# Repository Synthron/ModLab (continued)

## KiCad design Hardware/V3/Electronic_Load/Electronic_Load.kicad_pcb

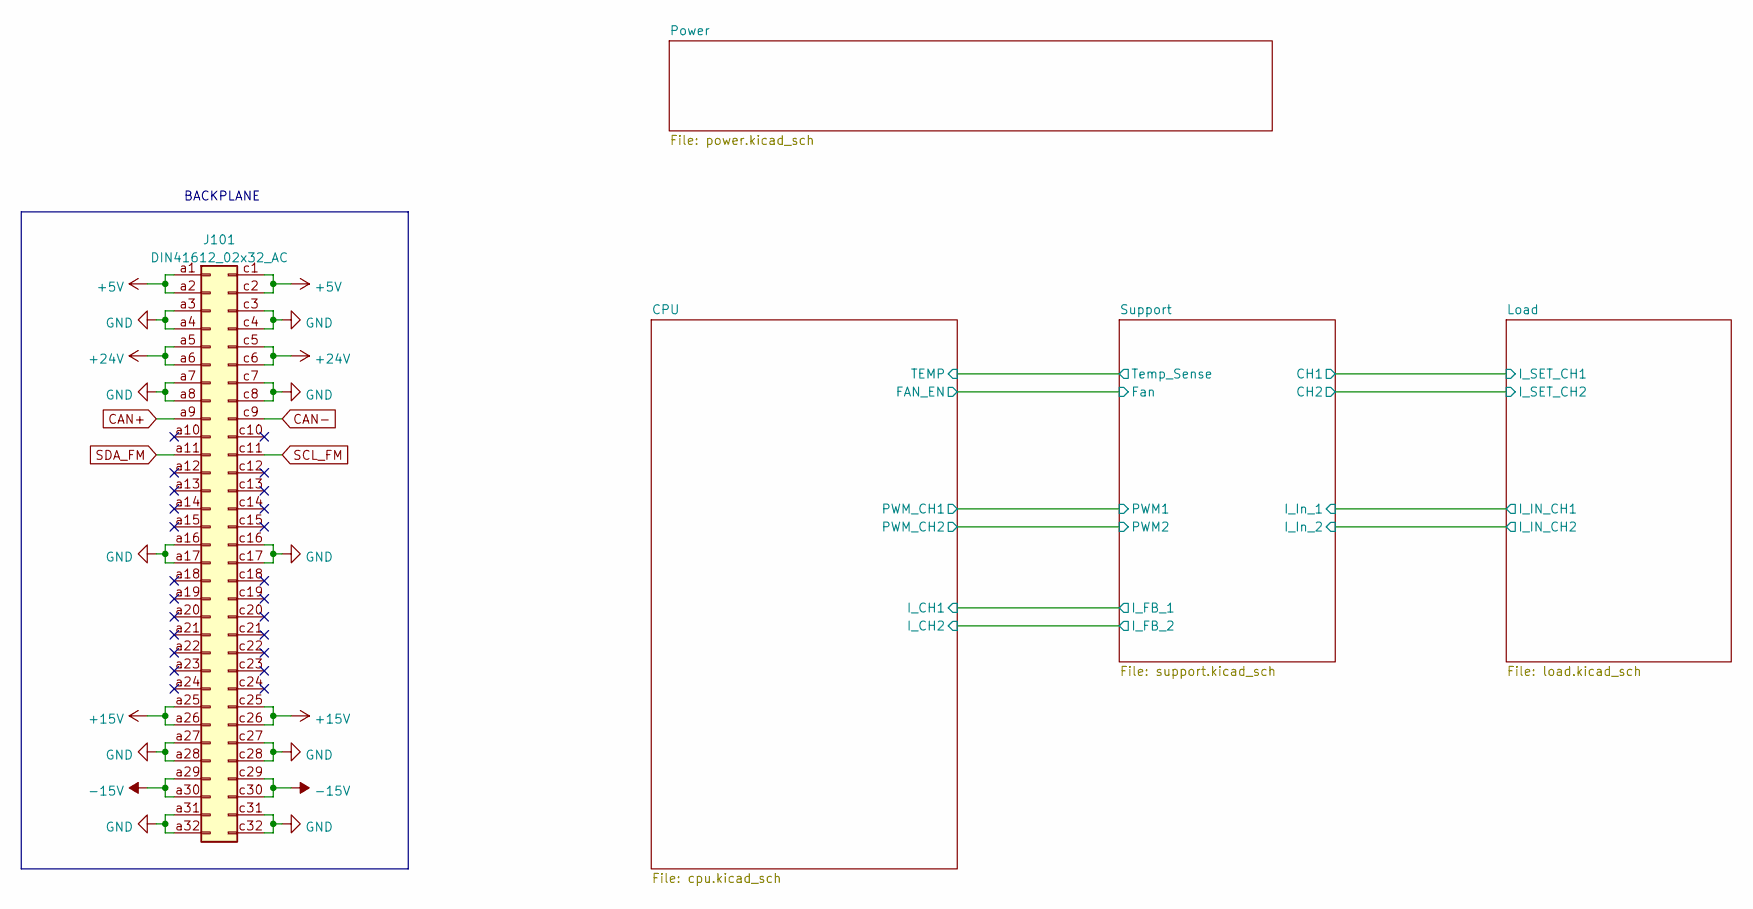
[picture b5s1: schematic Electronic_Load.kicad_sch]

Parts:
J101: DIN41612_02x32_AC; VG64_Euro

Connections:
+5V: J101.a1, J101.a2, J101.c1, J101.c2; also elsewhere on the board
+15V: J101.a25, J101.a26, J101.c25, J101.c26; also elsewhere on the board
+24V: J101.a5, J101.a6, J101.c5, J101.c6; also elsewhere on the board
-15V: J101.a29, J101.a30, J101.c29, J101.c30; also elsewhere on the board
CAN+: J101.a9; also elsewhere on the board
CAN-: J101.c9; also elsewhere on the board
GND: J101.a3, J101.a4, J101.a7, J101.a8, J101.a16, J101.a17, J101.a27, J101.a28, J101.a31, J101.a32, J101.c3, J101.c4, J101.c7, J101.c8, J101.c16, J101.c17, J101.c27, J101.c28, J101.c31, J101.c32; also elsewhere on the board
SCL_FM: J101.c11; also elsewhere on the board
SDA_FM: J101.a11; also elsewhere on the board

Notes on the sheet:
BACKPLANE

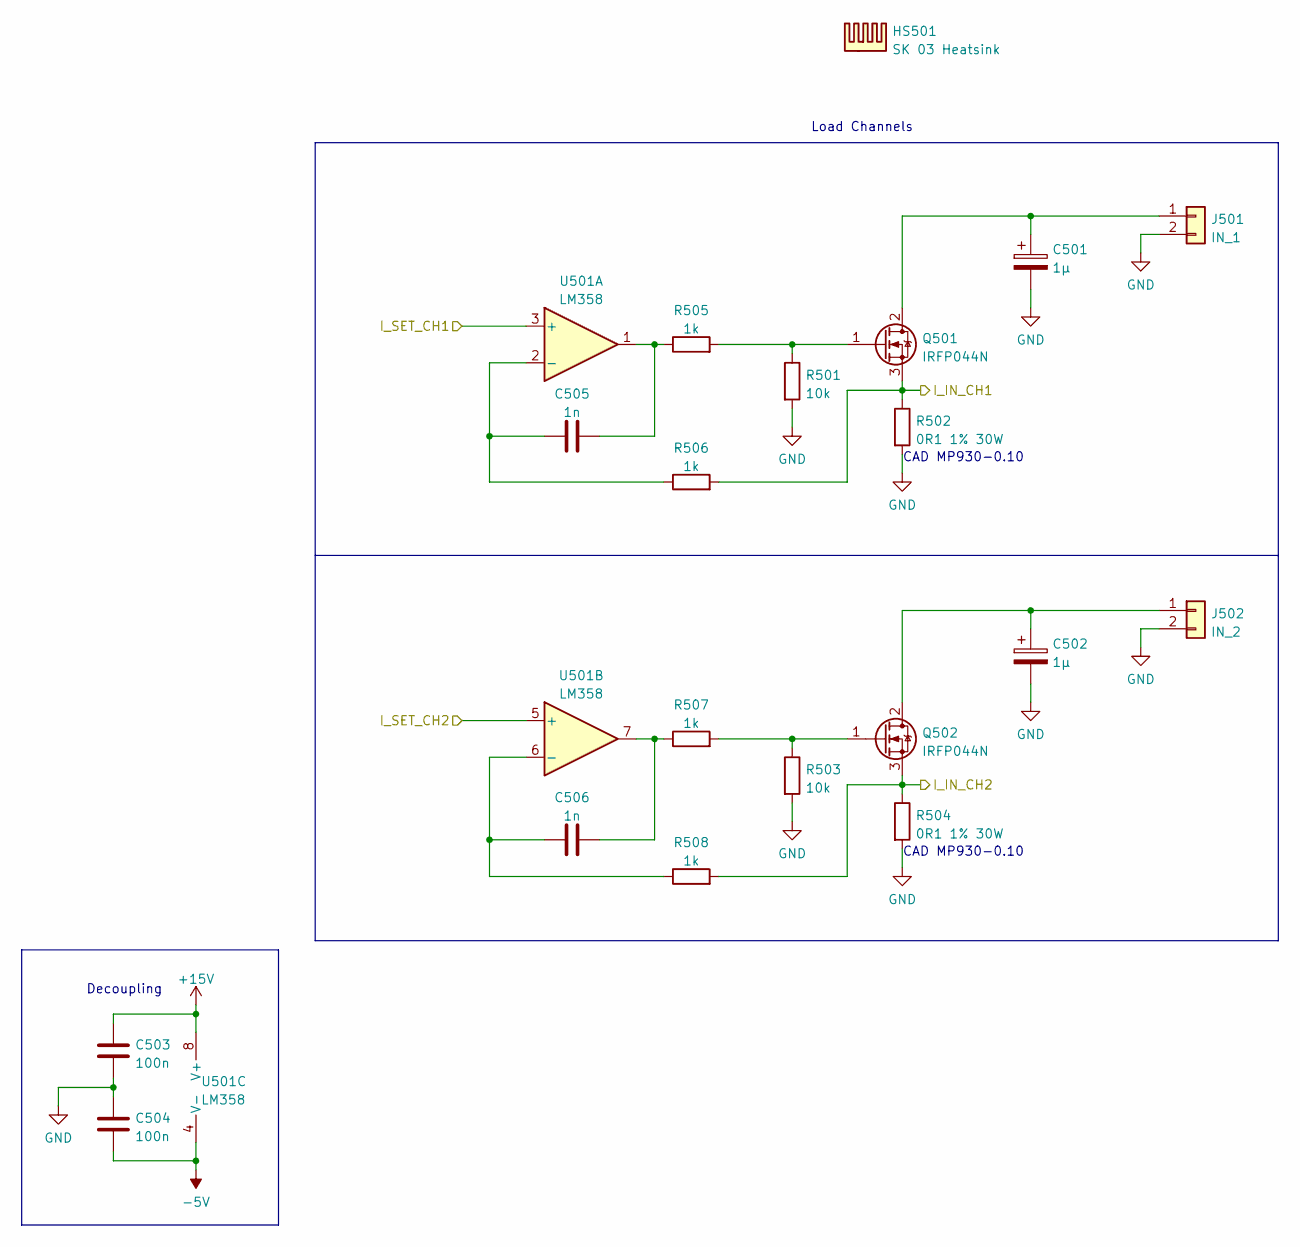
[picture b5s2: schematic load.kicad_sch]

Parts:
C501, C502: 1µ; CP_Radial_D5.0mm_P2.50mm
C503, C504: 100n; C_0805_2012Metric
C505, C506: 1n; C_0805_2012Metric
HS501: SK 03 Heatsink; SK-03
J501: IN_1; PinHeader_1x02_P2.54mm_Vertical
J502: IN_2; PinHeader_1x02_P2.54mm_Vertical
Q501, Q502: IRFP044N; TO-247-3_Horizontal_TabUp
R501, R503: 10k; R_0805_2012Metric
R502, R504: 0R1 1% 30W; TO-220F-2_Horizontal_TabUp
R505, R506, R507, R508: 1k; R_0805_2012Metric
U501: LM358; SOIC-8_3.9x4.9mm_P1.27mm

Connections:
+15V: C503.1, U501.8 (V+); also elsewhere on the board
-5V: C504.2, U501.4 (V-); also elsewhere on the board
/Load/I_IN_CH1: Q501.3 (S), R502.1, R506.2; also elsewhere on the board
/Load/I_IN_CH2: Q502.3 (S), R504.1, R508.2; also elsewhere on the board
/Load/I_SET_CH1: U501.3 (+); also elsewhere on the board
/Load/I_SET_CH2: U501.5 (+); also elsewhere on the board
GND: C501.2, C502.2, C503.2, C504.1, J501.2, J502.2, R501.2, R502.2, R503.2, R504.2; also elsewhere on the board
unnamed: C501.1, J501.1, Q501.2 (D)
unnamed: C502.1, J502.1, Q502.2 (D)
unnamed: Q501.1 (G), R501.1, R505.2
unnamed: Q502.1 (G), R503.1, R507.2
unnamed: C505.2, R505.1, U501.1
unnamed: C505.1, R506.1, U501.2 (-)
unnamed: C506.1, R508.1, U501.6 (-)
unnamed: C506.2, R507.1, U501.7

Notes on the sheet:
CAD MP930-0.10
Load Channels
Decoupling

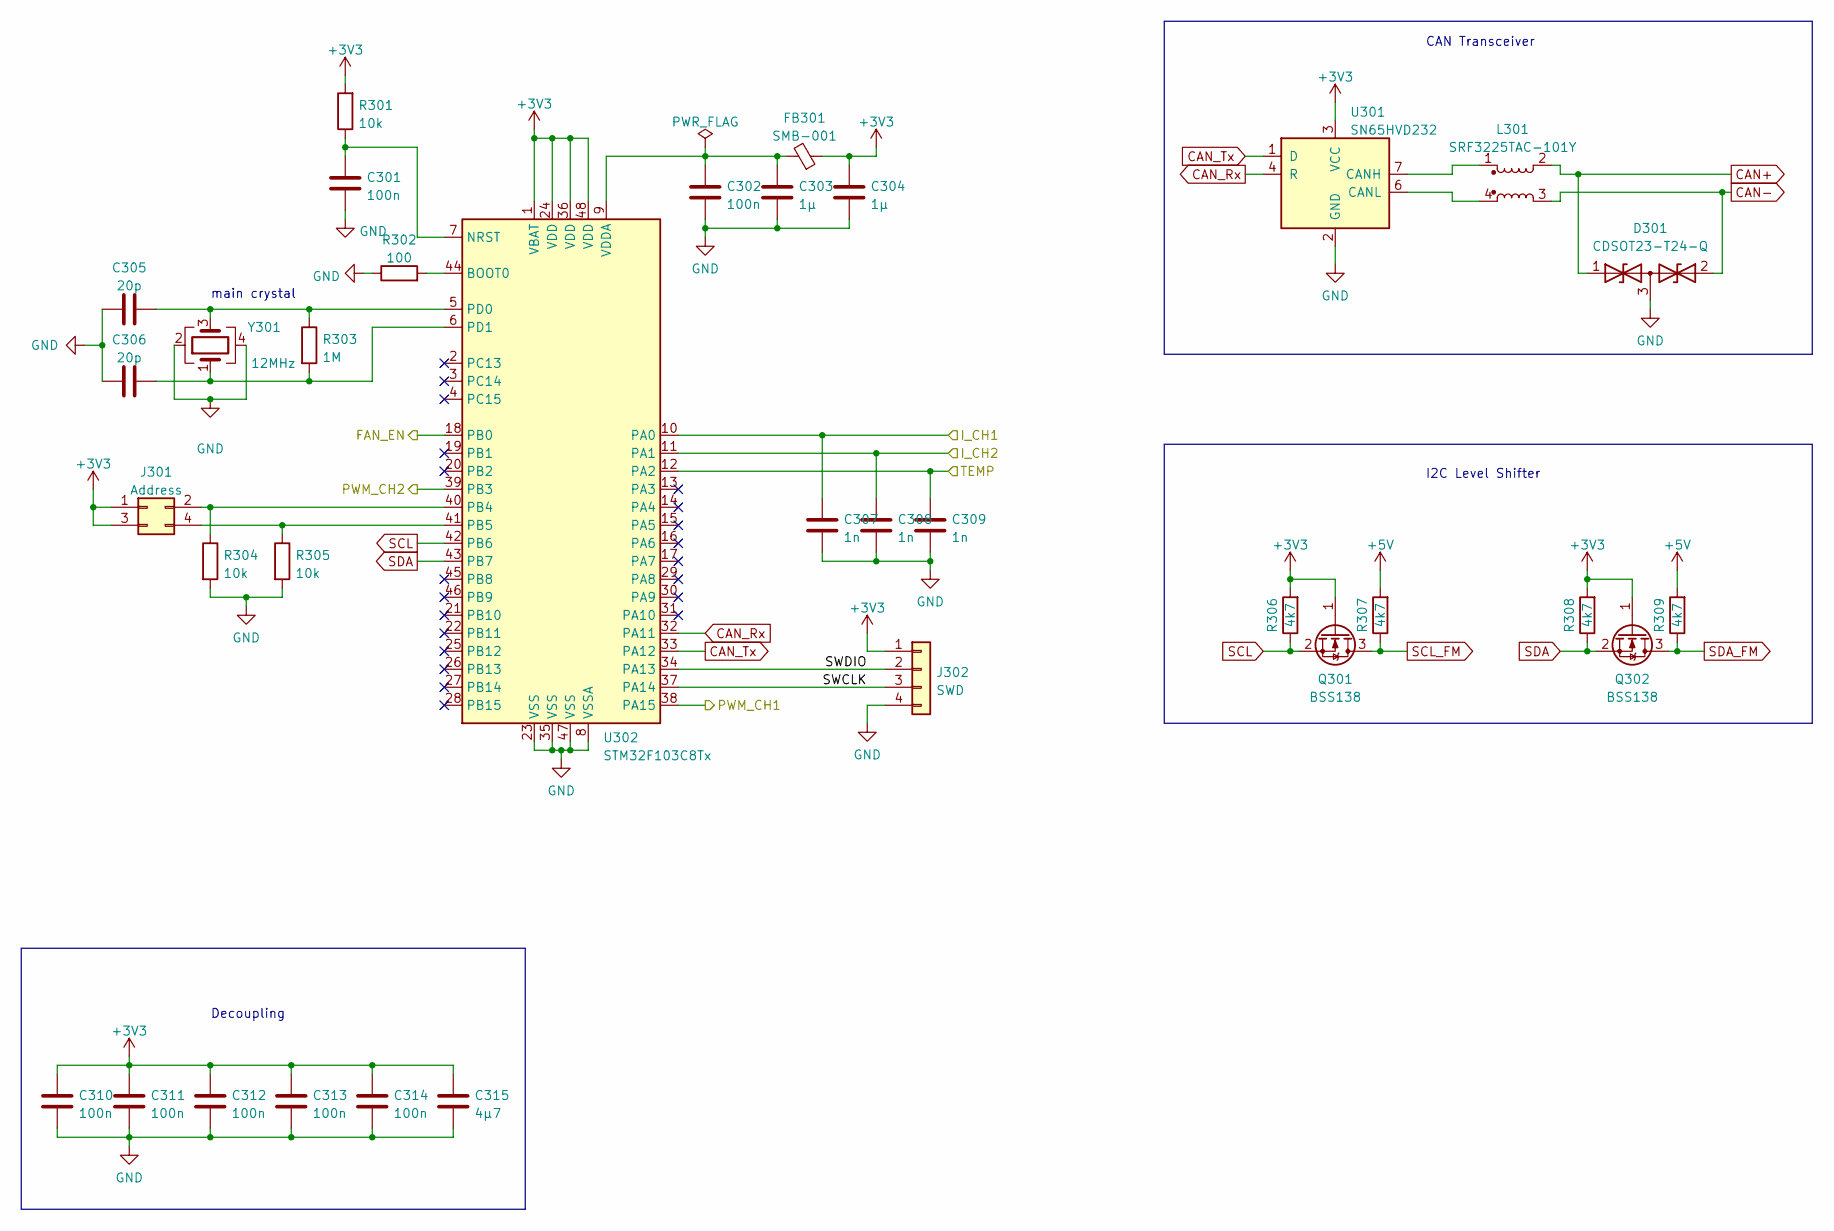
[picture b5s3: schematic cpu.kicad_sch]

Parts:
C301, C302, C310, C311, C312, C313, C314: 100n; C_0805_2012Metric
C303, C304: 1µ; C_0805_2012Metric
C305, C306: 20p; C_0805_2012Metric
C307, C308, C309: 1n; C_0805_2012Metric
C315: 4µ7; C_0805_2012Metric
D301: CDSOT23-T24-Q; SOT-23
FB301: SMB-001
J301: Address; PinHeader_2x02_P2.54mm_Vertical
J302: SWD; JST_XH_B4B-XH-A_1x04_P2.50mm_Vertical
L301: SRF3225TAC-101Y; SRF3225TAC
Q301, Q302: BSS138; SOT-23
R301, R304, R305: 10k; R_0805_2012Metric
R302: 100; R_0805_2012Metric
R303: 1M; R_0805_2012Metric
R306, R307, R308, R309: 4k7; R_0805_2012Metric
U301: SN65HVD232; SOIC-8_3.9x4.9mm_P1.27mm
U302: STM32F103C8Tx; LQFP-48_7x7mm_P0.5mm
Y301: 12MHz; Crystal_SMD_5032-4Pin_5.0x3.2mm

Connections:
+3V3: C304.1, C310.1, C311.1, C312.1, C313.1, C314.1, C315.1, FB301.1, J301.1, J301.3, J302.1, Q301.1 (G), Q302.1 (G), R301.2, R306.2, R308.2, U301.3 (VCC), U302.1 (VBAT), U302.24 (VDD), U302.36 (VDD), U302.48 (VDD); also elsewhere on the board
+5V: R307.2, R309.2; also elsewhere on the board
/CPU/FAN_EN: U302.18 (PB0); also elsewhere on the board
/CPU/I_CH1: C307.1, U302.10 (PA0); also elsewhere on the board
/CPU/I_CH2: C308.1, U302.11 (PA1); also elsewhere on the board
/CPU/PWM_CH1: U302.38 (PA15); also elsewhere on the board
/CPU/PWM_CH2: U302.39 (PB3); also elsewhere on the board
/CPU/SWCLK: J302.3, U302.37 (PA14)
/CPU/SWDIO: J302.2, U302.34 (PA13)
/CPU/TEMP: C309.1, U302.12 (PA2); also elsewhere on the board
CAN+: D301.1 (A1), L301.2; also elsewhere on the board
CAN-: D301.2 (A2), L301.3; also elsewhere on the board
CAN_Rx: U301.4 (R), U302.32 (PA11)
CAN_Tx: U301.1 (D), U302.33 (PA12)
GND: C301.2, C302.2, C303.2, C304.2, C305.1, C306.1, C307.2, C308.2, C309.2, C310.2, C311.2, C312.2, C313.2, C314.2, C315.2, D301.3 (common), J302.4, R302.1, R304.2, R305.2, U301.2 (GND), U302.8 (VSSA), U302.23 (VSS), U302.35 (VSS), U302.47 (VSS), Y301.2, Y301.4; also elsewhere on the board
unnamed: C301.1, R301.1, U302.7 (NRST)
unnamed: C302.1, C303.1, FB301.2, U302.9 (VDDA)
unnamed: C305.2, R303.1, U302.5 (PD0), Y301.3
unnamed: C306.2, R303.2, U302.6 (PD1), Y301.1
unnamed: J301.2, R304.1, U302.40 (PB4)
unnamed: J301.4, R305.1, U302.41 (PB5)
unnamed: L301.1, U301.7 (CANH)
unnamed: L301.4, U301.6 (CANL)
unnamed: R302.2, U302.44 (BOOT0)
SCL: Q301.2 (S), R306.1, U302.42 (PB6)
SCL_FM: Q301.3 (D), R307.1; also elsewhere on the board
SDA: Q302.2 (S), R308.1, U302.43 (PB7)
SDA_FM: Q302.3 (D), R309.1; also elsewhere on the board

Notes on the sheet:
Decoupling
I2C Level Shifter
CAN Transceiver
main crystal

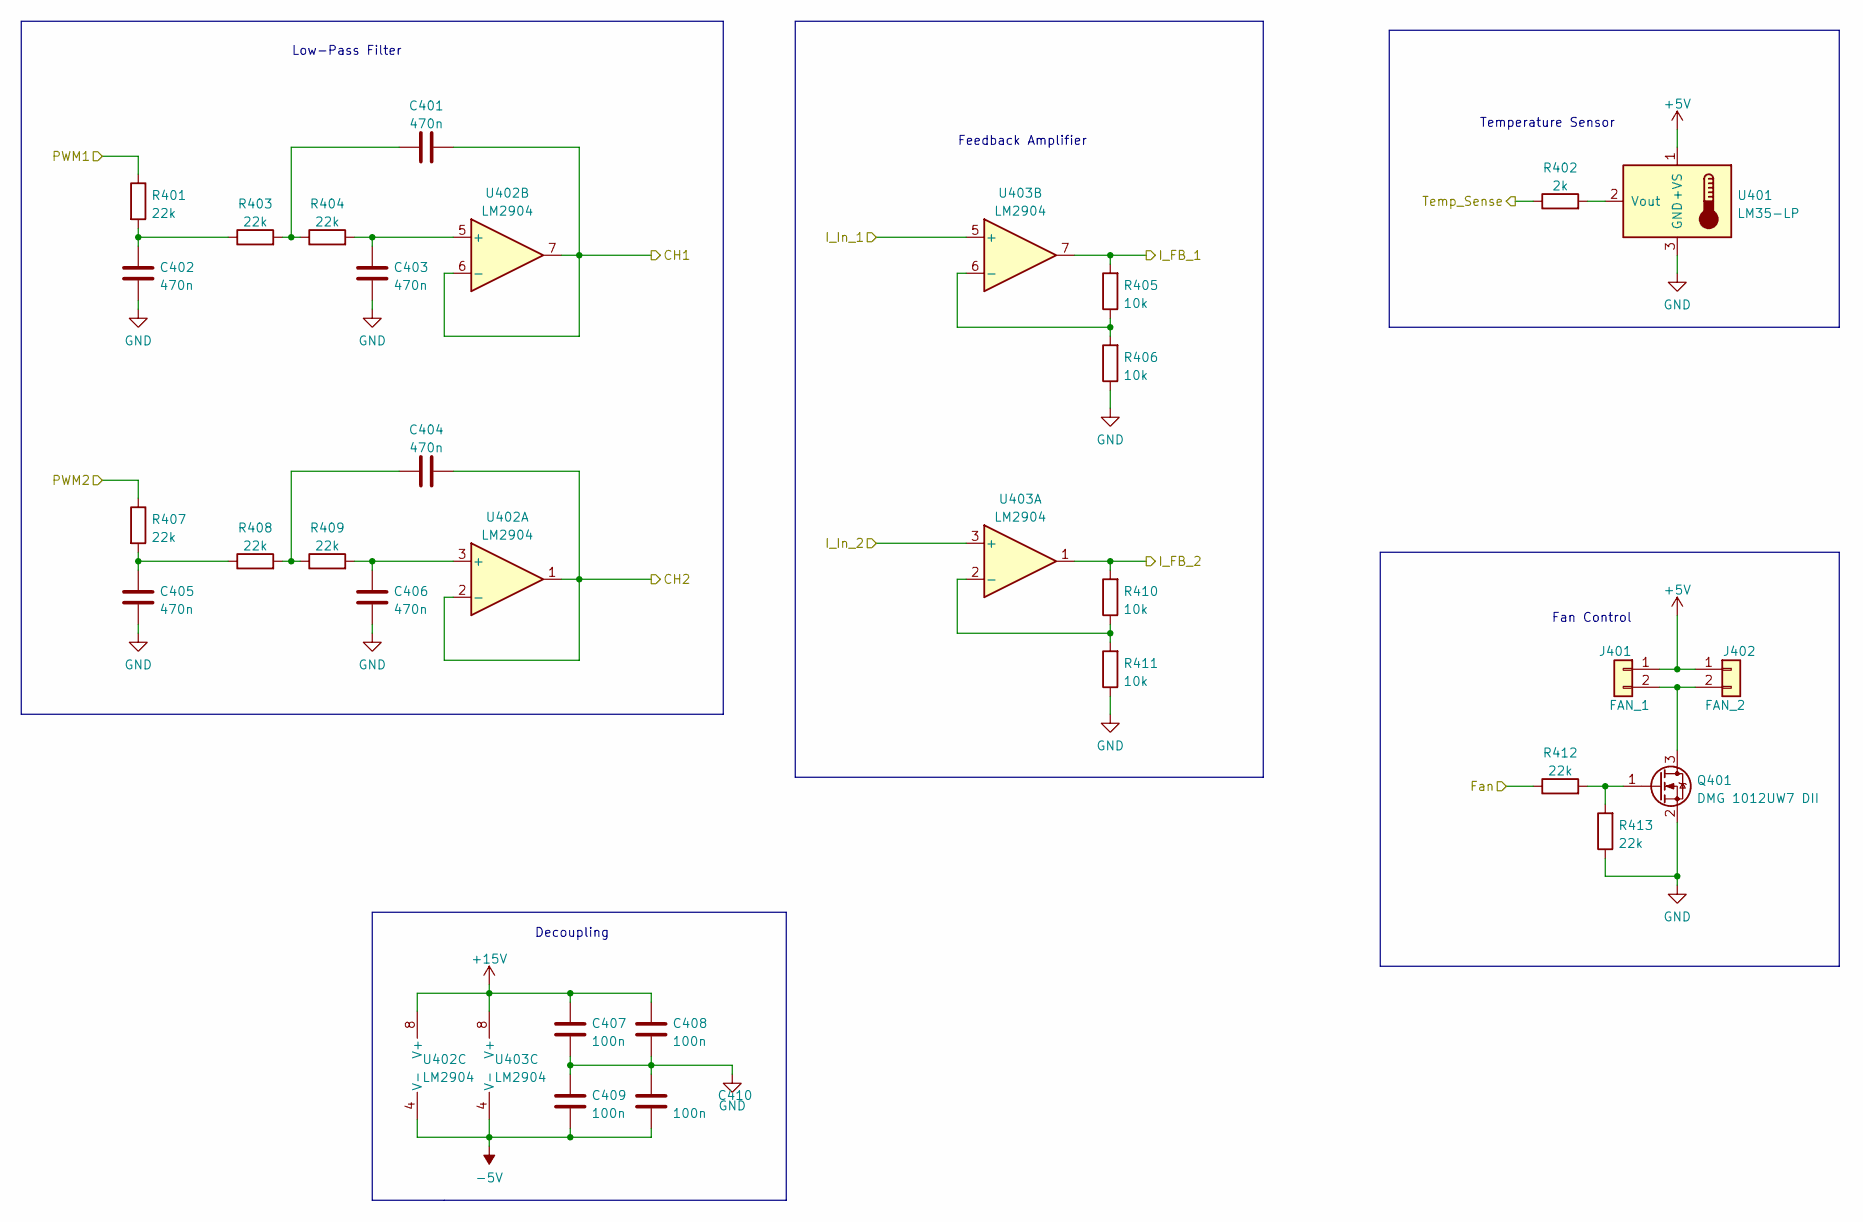
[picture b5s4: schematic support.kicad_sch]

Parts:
C401, C402, C403, C404, C405, C406: 470n; C_0805_2012Metric
C407, C408, C409, C410: 100n; C_0805_2012Metric
J401: FAN_1; PinHeader_1x02_P2.54mm_Vertical
J402: FAN_2; PinHeader_1x02_P2.54mm_Vertical
Q401: DMG 1012UW7 DII; SOT-323_SC-70
R401, R403, R404, R407, R408, R409, R412, R413: 22k; R_0805_2012Metric
R402: 2k; R_0805_2012Metric
R405, R406, R410, R411: 10k; R_0805_2012Metric
U401: LM35-LP; TO-92
U402, U403: LM2904; SOIC-8_3.9x4.9mm_P1.27mm

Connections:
+5V: J401.1, J402.1, U401.1 (+VS); also elsewhere on the board
+15V: C407.1, C408.1, U402.8 (V+), U403.8 (V+); also elsewhere on the board
-5V: C409.2, C410.2, U402.4 (V-), U403.4 (V-); also elsewhere on the board
/CPU/FAN_EN: R412.1; also elsewhere on the board
/CPU/I_CH1: R405.2, U403.7; also elsewhere on the board
/CPU/I_CH2: R410.2, U403.1; also elsewhere on the board
/CPU/PWM_CH1: R401.1; also elsewhere on the board
/CPU/PWM_CH2: R407.1; also elsewhere on the board
/CPU/TEMP: R402.1; also elsewhere on the board
/Load/I_IN_CH1: U403.5 (+); also elsewhere on the board
/Load/I_IN_CH2: U403.3 (+); also elsewhere on the board
/Load/I_SET_CH1: C401.2, U402.6 (-), U402.7; also elsewhere on the board
/Load/I_SET_CH2: C404.2, U402.1, U402.2 (-); also elsewhere on the board
GND: C402.2, C403.2, C405.2, C406.2, C407.2, C408.2, C409.1, C410.1, Q401.2 (S), R406.1, R411.1, R413.1, U401.3 (GND); also elsewhere on the board
unnamed: C401.1, R403.2, R404.1
unnamed: C402.1, R401.2, R403.1
unnamed: C403.1, R404.2, U402.5 (+)
unnamed: C404.1, R408.2, R409.1
unnamed: C405.1, R407.2, R408.1
unnamed: C406.1, R409.2, U402.3 (+)
unnamed: J401.2, J402.2, Q401.3 (D)
unnamed: Q401.1 (G), R412.2, R413.2
unnamed: R402.2, U401.2 (Vout)
unnamed: R405.1, R406.2, U403.6 (-)
unnamed: R410.1, R411.2, U403.2 (-)

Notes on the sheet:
Decoupling
Fan Control
Feedback Amplifier
Low-Pass Filter
Temperature Sensor

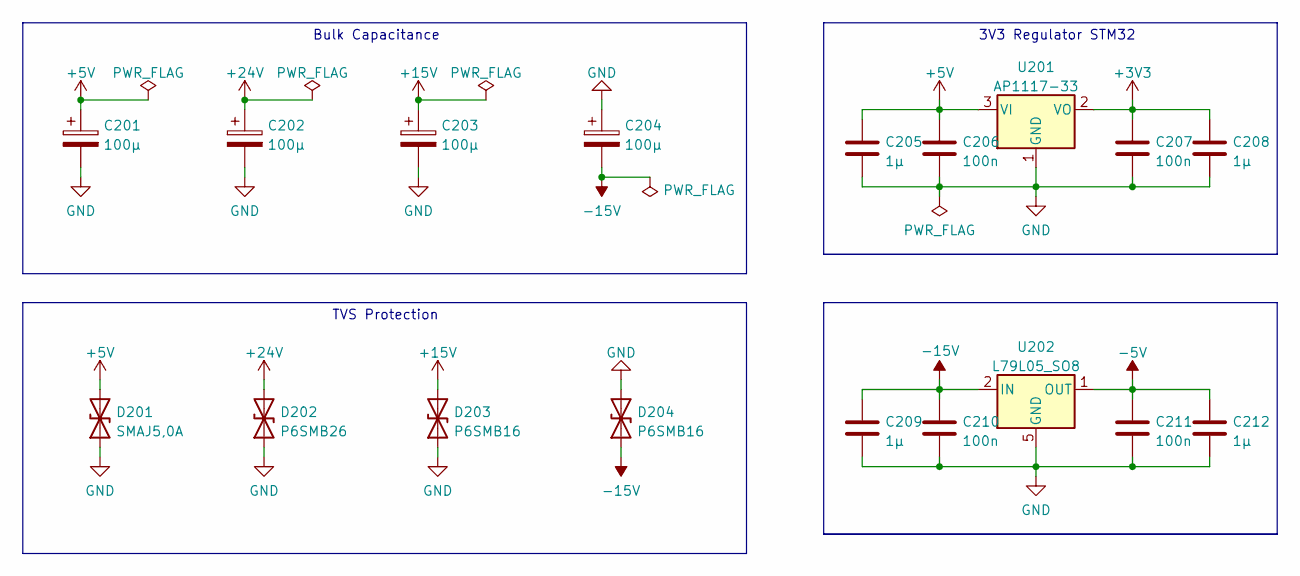
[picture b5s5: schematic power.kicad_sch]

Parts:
C201, C202, C203, C204: 100µ; CP_Radial_D8.0mm_P5.00mm
C205, C208, C209, C212: 1µ; C_0805_2012Metric
C206, C207, C210, C211: 100n; C_0805_2012Metric
D201: SMAJ5,0A; D_SMA
D202: P6SMB26; D_SMA
D203, D204: P6SMB16; D_SMA
U201: AP1117-33; SOT-223-3_TabPin2
U202: L79L05_SO8; SOIC-8_3.9x4.9mm_P1.27mm

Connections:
+3V3: C207.1, C208.1, U201.2 (VO); also elsewhere on the board
+5V: C201.1, C205.1, C206.1, D201.2 (A2), U201.3 (VI); also elsewhere on the board
+15V: C203.1, D203.2 (A2); also elsewhere on the board
+24V: C202.1, D202.2 (A2); also elsewhere on the board
-5V: C211.1, C212.1, U202.1 (OUT); also elsewhere on the board
-15V: C204.2, C209.1, C210.1, D204.1 (A1), U202.2 (IN), U202.3 (IN), U202.6 (IN), U202.7 (IN); also elsewhere on the board
GND: C201.2, C202.2, C203.2, C204.1, C205.2, C206.2, C207.2, C208.2, C209.2, C210.2, C211.2, C212.2, D201.1 (A1), D202.1 (A1), D203.1 (A1), D204.2 (A2), U201.1 (GND), U202.5 (GND); also elsewhere on the board

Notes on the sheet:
TVS Protection
Bulk Capacitance
3V3 Regulator STM32

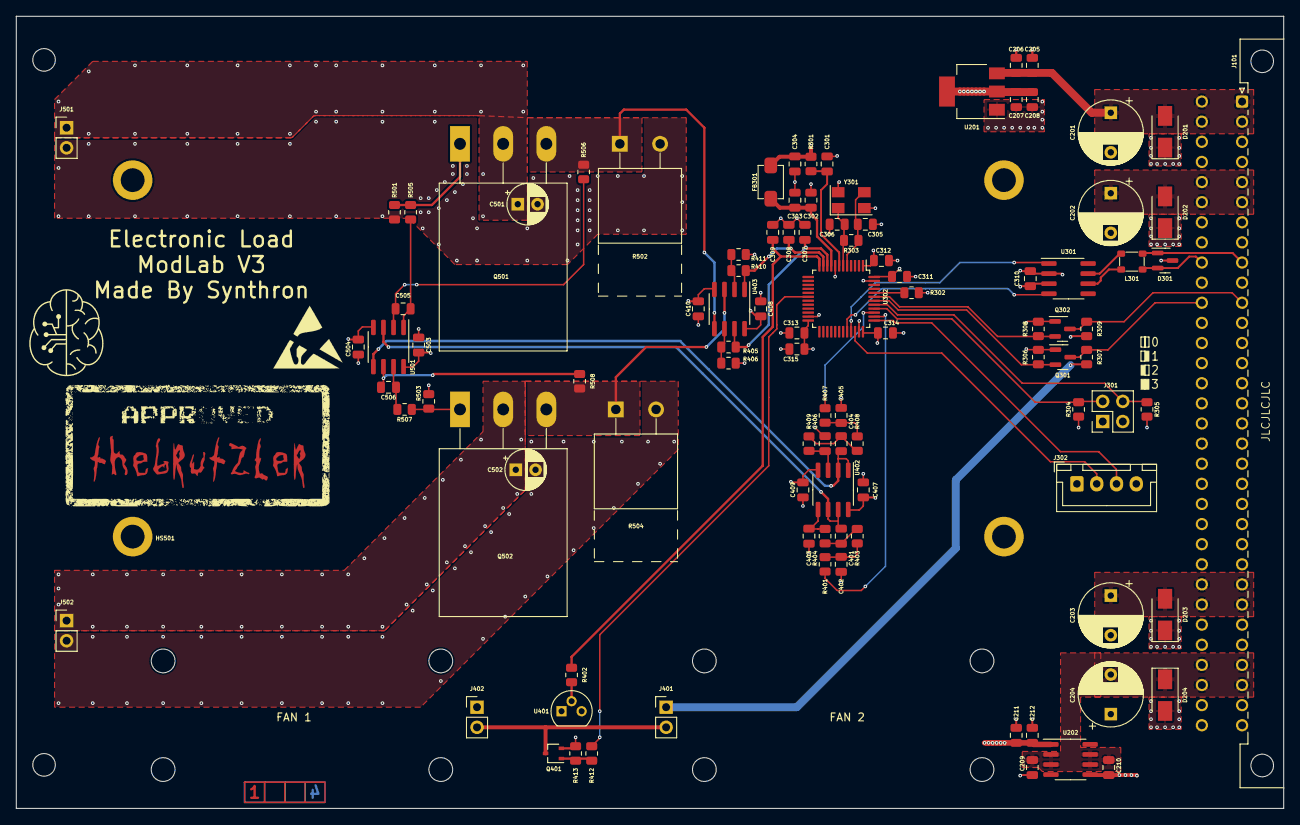
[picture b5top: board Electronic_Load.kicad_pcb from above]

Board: 4 copper layers, 160.0 x 100.0 mm, 102 parts (0 on the bottom side), 55 nets.

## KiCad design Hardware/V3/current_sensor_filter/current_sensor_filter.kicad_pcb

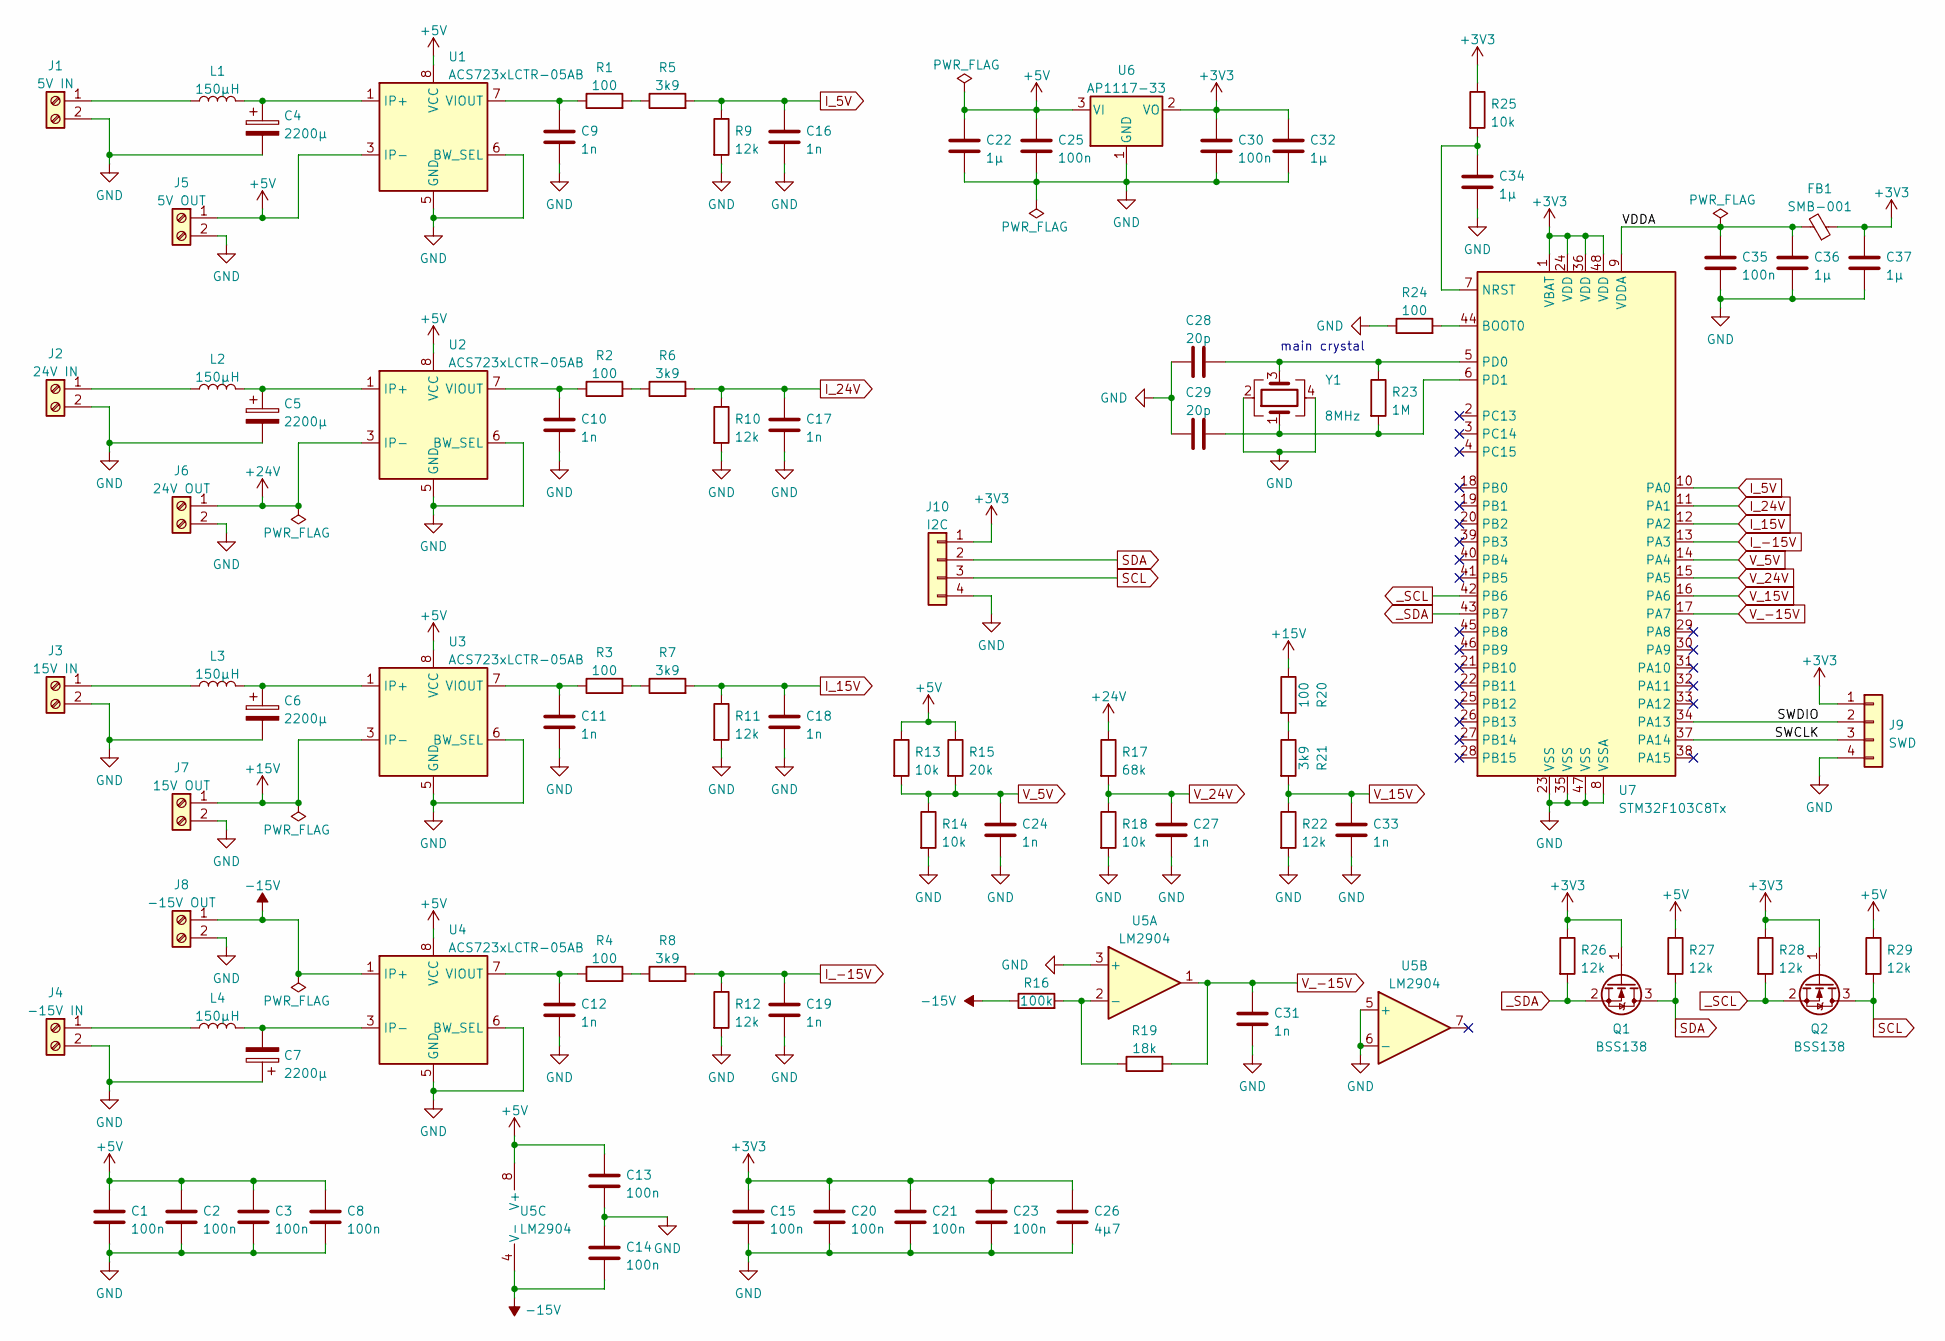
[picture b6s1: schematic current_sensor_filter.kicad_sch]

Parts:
C1, C2, C3, C8, C13, C14, C15, C20, C21, C23, C25, C30, C35: 100n; C_0805_2012Metric
C4, C5, C6, C7: 2200µ; CP_Radial_D12.5mm_P5.00mm
C9, C10, C11, C12, C16, C17, C18, C19, C24, C27, C31, C33: 1n; C_0805_2012Metric
C22, C32, C34, C36, C37: 1µ; C_0805_2012Metric
C26: 4µ7; C_0805_2012Metric
C28, C29: 20p; C_0805_2012Metric
FB1: SMB-001
J1: 5V IN; TerminalBlock_bornier-2_P5.08mm
J2: 24V IN; TerminalBlock_bornier-2_P5.08mm
J3: 15V IN; TerminalBlock_bornier-2_P5.08mm
J4: -15V IN; TerminalBlock_bornier-2_P5.08mm
J5: 5V OUT; TerminalBlock_bornier-2_P5.08mm
J6: 24V OUT; TerminalBlock_bornier-2_P5.08mm
J7: 15V OUT; TerminalBlock_bornier-2_P5.08mm
J8: -15V OUT; TerminalBlock_bornier-2_P5.08mm
J9: SWD; JST_XH_B4B-XH-A_1x04_P2.50mm_Vertical
J10: I2C; JST_XH_B4B-XH-A_1x04_P2.50mm_Vertical
L1, L2, L3, L4: 150µH; L_Toroid_Vertical_L25.4mm_W14.7mm_P12.20mm_Vishay_TJ5_BigPa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
Q1, Q2: BSS138; SOT-23
R1, R2, R3, R4, R20, R24: 100; R_0805_2012Metric
R5, R6, R7, R8, R21: 3k9; R_0805_2012Metric
R9, R10, R11, R12, R22, R26, R27, R28, R29: 12k; R_0805_2012Metric
R13, R14, R18, R25: 10k; R_0805_2012Metric
R15: 20k; R_0805_2012Metric
R16: 100k; R_0805_2012Metric
R17: 68k; R_0805_2012Metric
R19: 18k; R_0805_2012Metric
R23: 1M; R_0805_2012Metric
U1, U2, U3, U4: ACS723xLCTR-05AB; SOIC-8_3.9x4.9mm_P1.27mm
U5: LM2904; SOIC-8_3.9x4.9mm_P1.27mm
U6: AP1117-33; SOT-223-3_TabPin2
U7: STM32F103C8Tx; LQFP-48_7x7mm_P0.5mm
Y1: 8MHz; Crystal_SMD_5032-4Pin_5.0x3.2mm

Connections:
+3V3: C15.1, C20.1, C21.1, C23.1, C26.1, C30.1, C32.1, C37.1, FB1.1, J9.1, J10.1, Q1.1 (G), Q2.1 (G), R25.1, R26.1, R28.1, U6.2 (VO), U7.1 (VBAT), U7.24 (VDD), U7.36 (VDD), U7.48 (VDD)
+5V: C1.1, C2.1, C3.1, C8.1, C13.1, C22.1, C25.1, J5.1, R13.1, R15.1, R27.1, R29.1, U1.3 (IP-), U1.4 (IP-), U1.8 (VCC), U2.8 (VCC), U3.8 (VCC), U4.8 (VCC), U5.8 (V+), U6.3 (VI)
+15V: J7.1, R20.1, U3.3 (IP-), U3.4 (IP-)
+24V: J6.1, R17.1, U2.3 (IP-), U2.4 (IP-)
-15V: C14.2, J8.1, R16.1, U4.1 (IP+), U4.2 (IP+), U5.4 (V-)
/SWCLK: J9.3, U7.37 (PA14)
/SWDIO: J9.2, U7.34 (PA13)
/VDDA: C35.1, C36.1, FB1.2, U7.9 (VDDA)
GND: C1.2, C2.2, C3.2, C4.2, C5.2, C6.2, C7.1, C8.2, C9.2, C10.2, C11.2, C12.2, C13.2, C14.1, C15.2, C16.2, C17.2, C18.2, C19.2, C20.2, C21.2, C22.2, C23.2, C24.2, C25.2, C26.2, C27.2, C28.1, C29.1, C30.2, C31.2, C32.2, C33.2, C34.2, C35.2, C36.2, C37.2, J1.2, J2.2, J3.2, J4.2, J5.2, J6.2, J7.2, J8.2, J9.4, J10.4, R9.2, R10.2, R11.2, R12.2, R14.2, R18.2, R22.2, R24.1, U1.5 (GND), U1.6 (BW_SEL), U2.5 (GND), U2.6 (BW_SEL), U3.5 (GND), U3.6 (BW_SEL), U4.5 (GND), U4.6 (BW_SEL), U5.3 (+), U5.5 (+), U5.6 (-), U6.1 (GND), U7.8 (VSSA), U7.23 (VSS), U7.35 (VSS), U7.47 (VSS), Y1.2, Y1.4
I_5V: C16.1, R5.2, R9.1, U7.10 (PA0)
I_15V: C18.1, R7.2, R11.1, U7.12 (PA2)
I_24V: C17.1, R6.2, R10.1, U7.11 (PA1)
I_-15V: C19.1, R8.2, R12.1, U7.13 (PA3)
unnamed: C4.1, L1.2, U1.1 (IP+), U1.2 (IP+)
unnamed: C5.1, L2.2, U2.1 (IP+), U2.2 (IP+)
unnamed: C6.1, L3.2, U3.1 (IP+), U3.2 (IP+)
unnamed: C9.1, R1.1, U1.7 (VIOUT)
unnamed: C10.1, R2.1, U2.7 (VIOUT)
unnamed: C11.1, R3.1, U3.7 (VIOUT)
unnamed: C12.1, R4.1, U4.7 (VIOUT)
unnamed: C28.2, R23.1, U7.5 (PD0), Y1.3
unnamed: C29.2, R23.2, U7.6 (PD1), Y1.1
unnamed: C34.1, R25.2, U7.7 (NRST)
unnamed: J1.1, L1.1
unnamed: J2.1, L2.1
unnamed: J3.1, L3.1
unnamed: J4.1, L4.1
unnamed: C7.2, L4.2, U4.3 (IP-), U4.4 (IP-)
unnamed: R1.2, R5.1
unnamed: R2.2, R6.1
unnamed: R3.2, R7.1
unnamed: R4.2, R8.1
unnamed: R16.2, R19.1, U5.2 (-)
unnamed: R20.2, R21.1
unnamed: R24.2, U7.44 (BOOT0)
SCL: J10.3, Q2.3 (D), R29.2
SDA: J10.2, Q1.3 (D), R27.2
V_5V: C24.1, R13.2, R14.1, R15.2, U7.14 (PA4)
V_15V: C33.1, R21.2, R22.1, U7.16 (PA6)
V_24V: C27.1, R17.2, R18.1, U7.15 (PA5)
V_-15V: C31.1, R19.2, U5.1, U7.17 (PA7)
_SCL: Q2.2 (S), R28.2, U7.42 (PB6)
_SDA: Q1.2 (S), R26.2, U7.43 (PB7)

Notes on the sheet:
main crystal

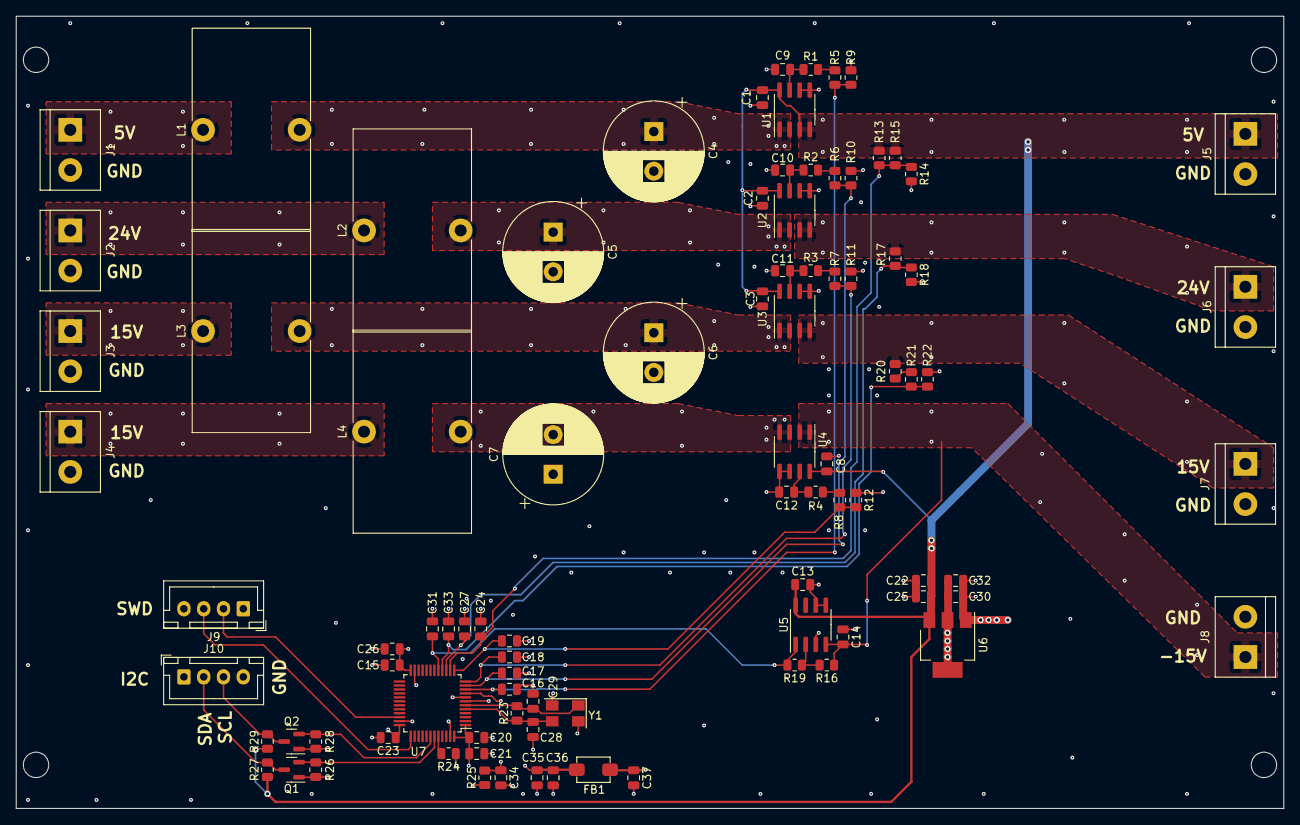
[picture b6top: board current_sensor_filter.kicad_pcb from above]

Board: 4 copper layers, 160.0 x 100.0 mm, 91 parts (0 on the bottom side), 43 nets.
